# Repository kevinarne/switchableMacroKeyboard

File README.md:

# Switchable Macro Keyboard
Many programs, such as Inkscape, have some pretty intricate keyboard shortcuts that I find challenging to use regularly, so I've made a macro keyboard that can be switched between different macro keyboards.

At the moment, the code only supports sending static strings, like "Hooray" or "Wow, that's crazy," but eventually it will also support modifier keys like shift and control.

# Components
* Arduino Pro Micro
* 12 x Cherry MX buttons
* 12 x diodes
* 3D printed housing
* 3D printed knob
* LCD Panel
* 7 x 10k ohm resistors
* 1 x rotary encoder
* Micro USB cable
* Custom PCB (see gerber.zip)

# Next Steps
* Encapsulate keyboard logic in an object
* Add long-press detection to keyboard and rotary encoder
* Add screen animations
* Create scripting language for complicated key sequences
* Remove old LCD code

# Programming
To program using the Arduino environment, make sure to set your board to Arduino Leonardo. There are several test sketches in the src/test folder that you can use to test individual components in isolation, but the main sketch is in the src/macroKeyMain folder along with the keyboards.h file that contains the different macro keyboards to be loaded.

If you simply want this to work as a macro keyboard, but with your own commands, you should only have to change the keyboards.h file and upload the code to your Arduino Pro Micro.

Note: the main sketch has no checks on any of the data in keyboards.h. Although the code may compile and upload, **failure to correctly format keyboards.h can result in index out of bounds errors, causing the keyboard to stop working until power cycled.**

You will need to have the following libraries installed:
* Wire.h
* LiquidCrystal_I2C.h
* Keyboard.h

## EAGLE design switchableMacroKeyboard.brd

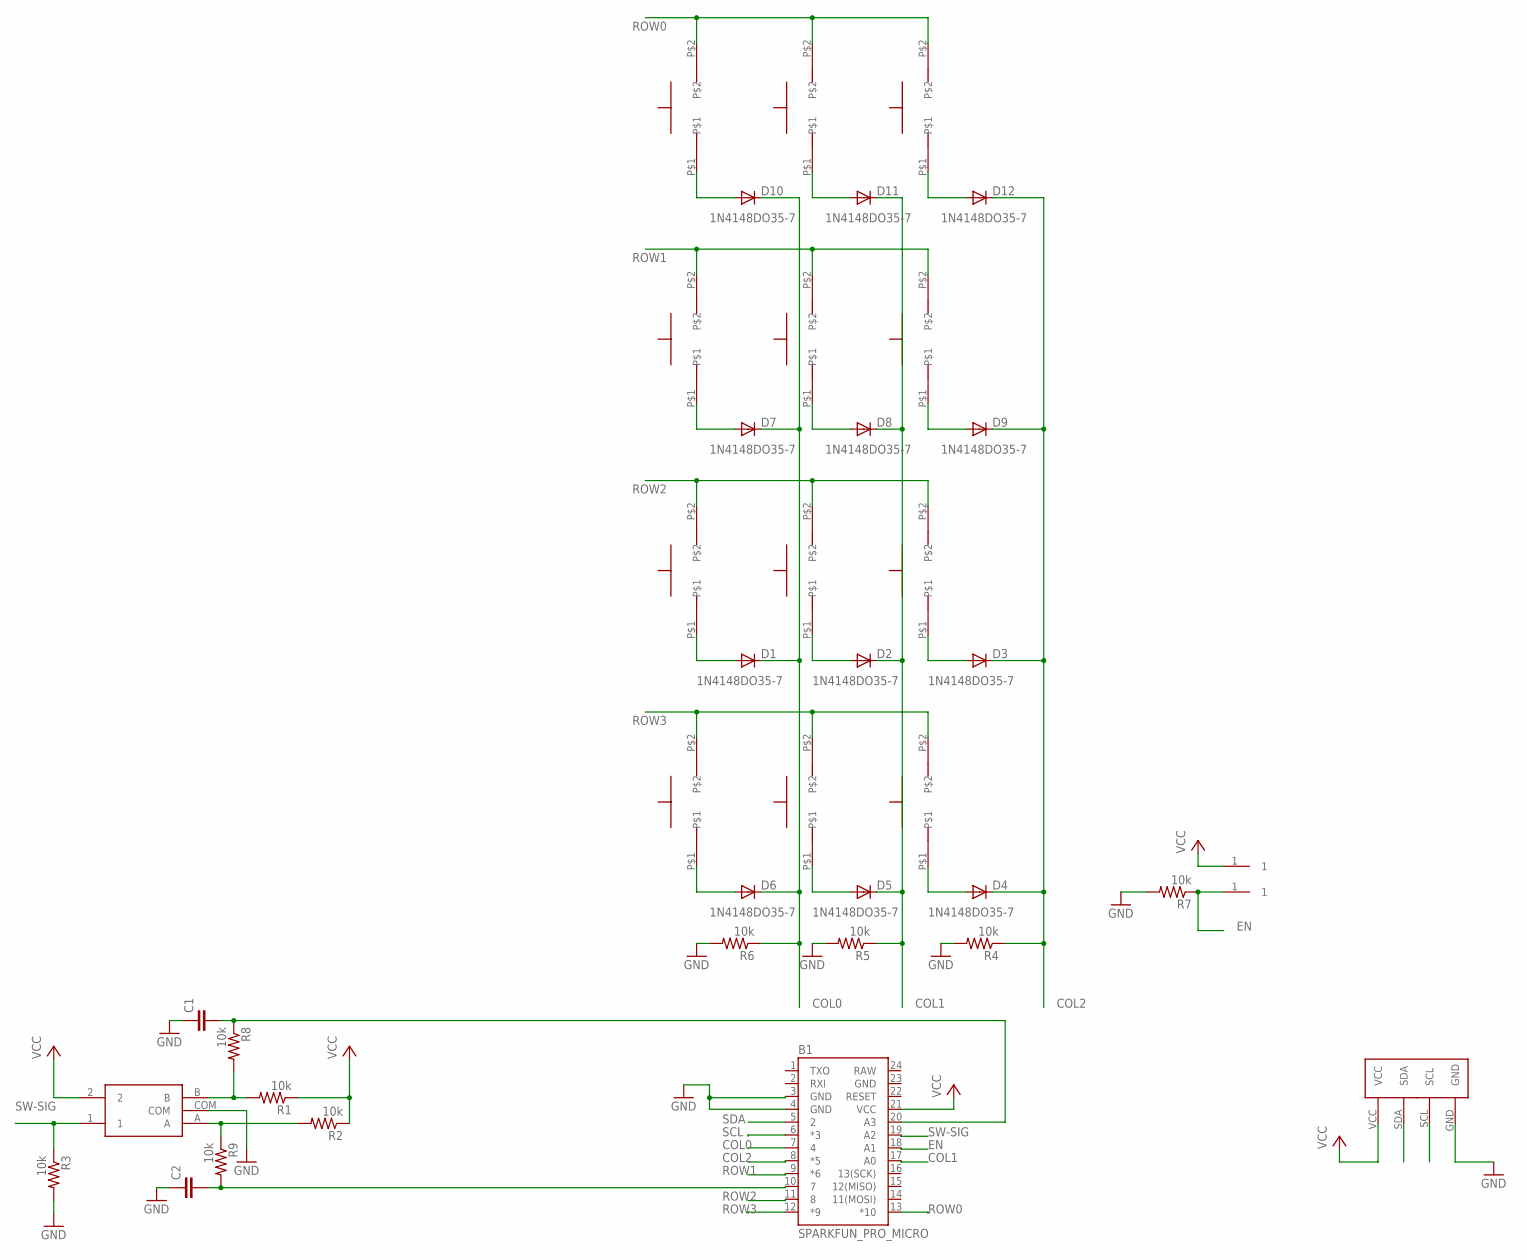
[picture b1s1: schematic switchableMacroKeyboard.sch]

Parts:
B1: SPARKFUN_PRO_MICRO
C1, C2: C5/2.5; C5B2.5
D1, D2, D3, D4, D5, D6, D7, D8, D9, D10, D11, D12: 1N4148DO35-7; DO35-7
R1, R2, R3, R4, R5, R6, R7, R8, R9: 10k; 0207/10
U$1, U$2: TESTPOINT
U$3: I2C-100MIL
U$4, U$5, U$6, U$7, U$8, U$9, U$10, U$11, U$12, U$14, U$15, U$16: CHERRYMXBLUE
U$13: RE-PEC11R-4315F-S0012

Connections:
COL0: B1.7 (4), D1.C, D6.C, D7.C, D10.C, R6.1
COL1: B1.17 (A0), D2.C, D5.C, D8.C, D11.C, R5.1
COL2: B1.8 (*5), D3.C, D4.C, D9.C, D12.C, R4.1
EN: B1.18 (A1), R7.1, U$2.1
GND: B1.3 (GND), B1.4 (GND), B1.23 (GND), C1.1, C2.1, R3.2, R4.2, R5.2, R6.2, R7.2, U$3.GND, U$13.COM
unnamed: B1.10 (7), C2.2, R9.2
unnamed: R1.2, R8.2, U$13.B
unnamed: D1.A, U$10.P$1
unnamed: D2.A, U$11.P$1
unnamed: D3.A, U$12.P$1
unnamed: D6.A, U$14.P$1
unnamed: D5.A, U$15.P$1
unnamed: D4.A, U$16.P$1
unnamed: B1.20 (A3), C1.2, R8.1
unnamed: R2.2, R9.1, U$13.A
unnamed: D7.A, U$7.P$1
unnamed: D8.A, U$8.P$1
unnamed: D9.A, U$9.P$1
unnamed: D10.A, U$4.P$1
unnamed: D11.A, U$5.P$1
unnamed: D12.A, U$6.P$1
RAW: B1.24 (RAW)
ROW0: B1.13 (*10), U$4.P$2, U$5.P$2, U$6.P$2
ROW1: B1.9 (*6), U$7.P$2, U$8.P$2, U$9.P$2
ROW2: B1.11 (8), U$10.P$2, U$11.P$2, U$12.P$2
ROW3: B1.12 (*9), U$14.P$2, U$15.P$2, U$16.P$2
SCL: B1.6 (*3), U$3.SCL
SDA: B1.5 (2), U$3.SDA
SW-SIG: B1.19 (A2), R3.1, U$13.1
VCC: B1.21 (VCC), R1.1, R2.1, U$1.1, U$3.VCC, U$13.2

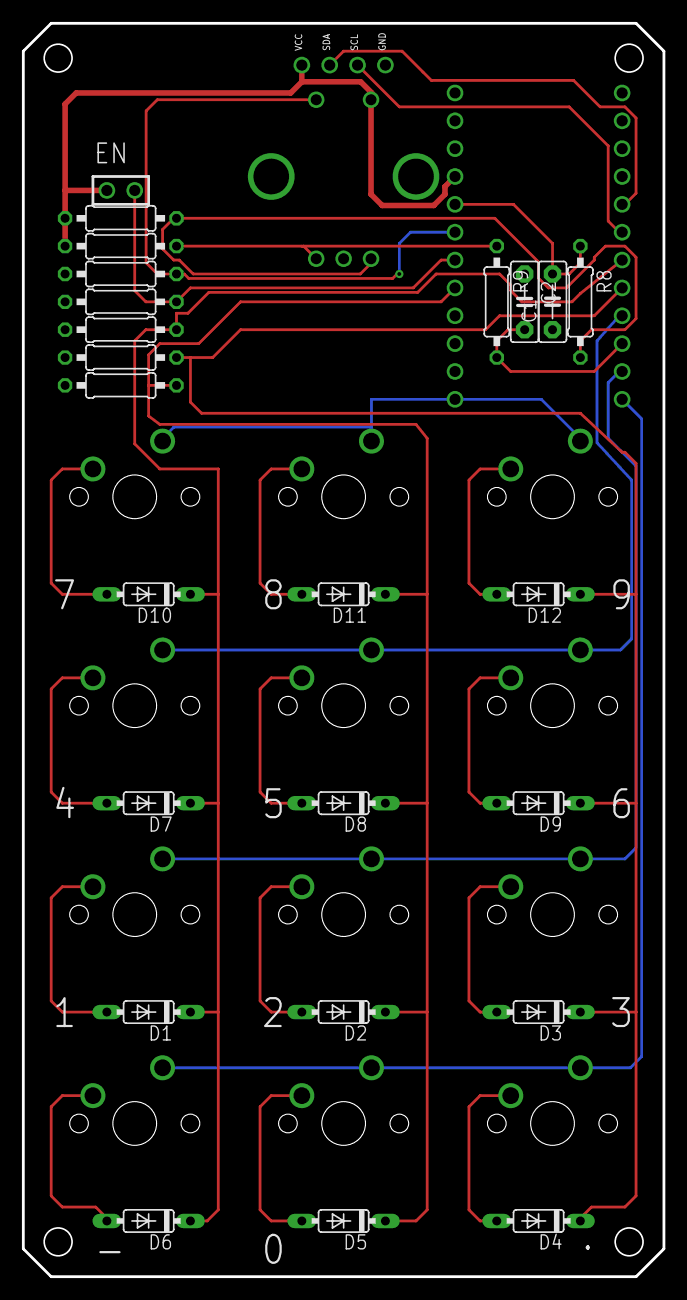
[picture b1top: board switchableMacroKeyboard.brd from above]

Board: 2 copper layers, 58.4 x 114.3 mm, 40 parts (1 on the bottom side), 29 nets.

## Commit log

2020-04-21 Initial commit. Copied schematic from original design, added some more buttons (need wiring) and removed the header for the rotary encoder. To do: wire the new buttons, change buttons to tactile butt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
2020-04-21 Added blank Arduino files. To do: Add a switch to the input so it can be debugged appropriately.
2020-04-22 Added some pseudo code to source. Connected the switches to the Pro Micro
2020-04-22 Made rotary encoder footprint and symbol. Wired rotary encoder to Pro Micro. Added LCD breakout points. To do: replace switches with tactile switches, add an enable pin (2-pin jumper), and route.
2020-04-22 Changed to tact switches.
2020-04-22 Routed the entire board and added pulldown resistors to the columns. To do: sleep on it and order in the morning.
2020-04-22 Added an enable option to disable all output when broken for debugging purposes. Mitered all of the traces with a 40 mil miter. Changed the corners from filets to chamfers.
2020-04-22 Added gerber files for the boards I ordered.
2020-04-25 Added some more pseudo code and added loops to the keyboard function.
2020-04-25 Added pin numbers and some pseudocode.
2020-04-26 Addedmore structure to the keyboard scanning, including some digital reads. Added a toBeSent matrix that helps with communication between the keyboardScanning function and main loop. To do: setup the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
2020-04-27 Added SoftwareSerial initialization.
2020-04-27 Added Keyboard #include and begin().
2020-04-27 Added details on bringing the first board version up to speed. Added some position variables to macroKeyMain for the rotary encoder.
2020-04-29 Added enable pin debugging.
2020-04-29 Addedfunction for outputting the keyboard input matrix to the Serial output.
2020-05-01 Added test scripts for rotary encoder and enable pin. Rotary encoder test script still needs fleshing out. To do: write keyboard test script.
2020-05-01 Wrote keypad test and ran it on the device (passed). To do: add logic to send a key once to the keypad test.
2020-05-01 Added key sending. Successfully only sends the key at the first press when holding. No sign of bouncing.
2020-05-01 Folded the keyboard test scripts back into the macroKeyMain script. To do: work on rotary encoder script.
2020-05-02 Switched around visible layers on board for exporting a dxf. Added code loading info to README.md.
2020-05-02 Added lots of detail to encoder test. Got the position to change with a rotation in either direction (can't tell the difference between the two yet), but in serious need of debouncing.
2020-05-02 Added a good amount of pause for debouncing to REncTest.ino. Appears to work for most cases, but still gets the occasional double.
2020-05-02 Added source for rotary encoder info to the top of REncTest.ino.
2020-05-03 Made rotary encoder only trigger when the clock pin is 1. Reduced delay to 50, seems to have helped with the reliability at higher rotation speeds.
2020-05-03 Integrated the rotary encoder code in macroKeyMain.
2020-05-05 Added I2C header for LCD panel. Rearranged pinouts to open up I2C pins on the Pro Micro. To do: add labels to I2C bus and reroute board.
2020-05-06 Partially rerouted board with several pins moved around on the microcontroller for ease of routing. To do: route columns on bottom layer.
2020-05-25 Added a header file to hold all of the keyboards. Added an LCD test that works.
2020-05-25 Fixed all of the pinouts to reflect the new board layout. Adjusted the rotary encoder test to represent the new pins as well.
2020-05-25 Integrated keyboard, rotary encoder, and header file. To do: add LCD code to display keyboard name, create language for sending unusual key presses together.
2020-05-25 Implemented LCD panel to display keyboard name.
2020-05-25 Reformatted a lot of the code, adding spacing to comments and moving curly brackets around.
2020-05-27 Updated README.md. Moved LCD panel control to a dedicated function in case I change to a different display panel at some point. Updated gerber file to reflect the newest version of the boards.
2020-05-31 Integrated String parsing to allow for modifier keys. Finally hooked up the actual Keyboard library and found it all works. To do: make a new enclosure including the LCD panel, code for the keyboards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
2020-06-05 Added an Inkscape keyboard. Having trouble getting the stroke to path - break apart - union sequence to work right.
2020-06-05 Switched the buttons to Cherry MX Blues, but found this may require a bigger board, mostly length-wise. Moving the diodes out of the way of the key has cramped things. To do: adjust board dimensions 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
2020-06-10 Adjusted the size of the board and rerouted.
2020-07-06 Moved the Pro Micro board up to reduce interference with the key switches. Adjusted routing accordingly. Ordered this version in green.
2020-07-11 Changed footprints for Cherry MX keys to use holes rather than circles on the Dimension layer due to an issue at the board manufacturer.
2020-07-16 Updated Cherry foot print to fix holes too small for the pins.
2020-07-16 Adjusted routing to allow for the changed switch footprint.
2021-03-19 Started conversion from Eagle to KiCAD. Created rudimentary rotary encoder schematic symbol and footprint based on previous Eagle iteration. Created new schematic symbol for Pro Micro using a more fu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
2021-03-19 Added footprint for Pro Micro, next is the footprint for the keys.
2021-03-21 Finished schematic sans OLED screen, generated net list, placed components on board.
2021-03-22 Board routed but missing OLED screen, corner chamfers, mounting holes, logo, and switch footprint fix.
2021-03-22 Updated the switch footprints, chamfered corners, added mounting holes. Still need to add logo, but then it'll be ready for manufacturing.
2021-03-23 Added logo to solder mask layer (will show the underlying copper fill there). Sending out for manufacturing.
2021-03-23 Added KiCad-generated gerbers for this iteration of the macro keyboard PCB.
2021-03-23 Removed old Eagle files.
2021-06-11 Updated README.md, made a mess of everything else. Next step is to clean up and add a .gitignore file.
2021-06-11 Added .gitignore to clean things up a good bit.

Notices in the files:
parts and their libraries:
SparkFun-Boards: Licensing: Creative Commons ShareAlike 4.0 International - https://creativecommons.org/licenses/by-sa/4.0
